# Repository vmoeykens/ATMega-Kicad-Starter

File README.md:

# ATMega328P KiCad Starter Board
Vincent Moeykens

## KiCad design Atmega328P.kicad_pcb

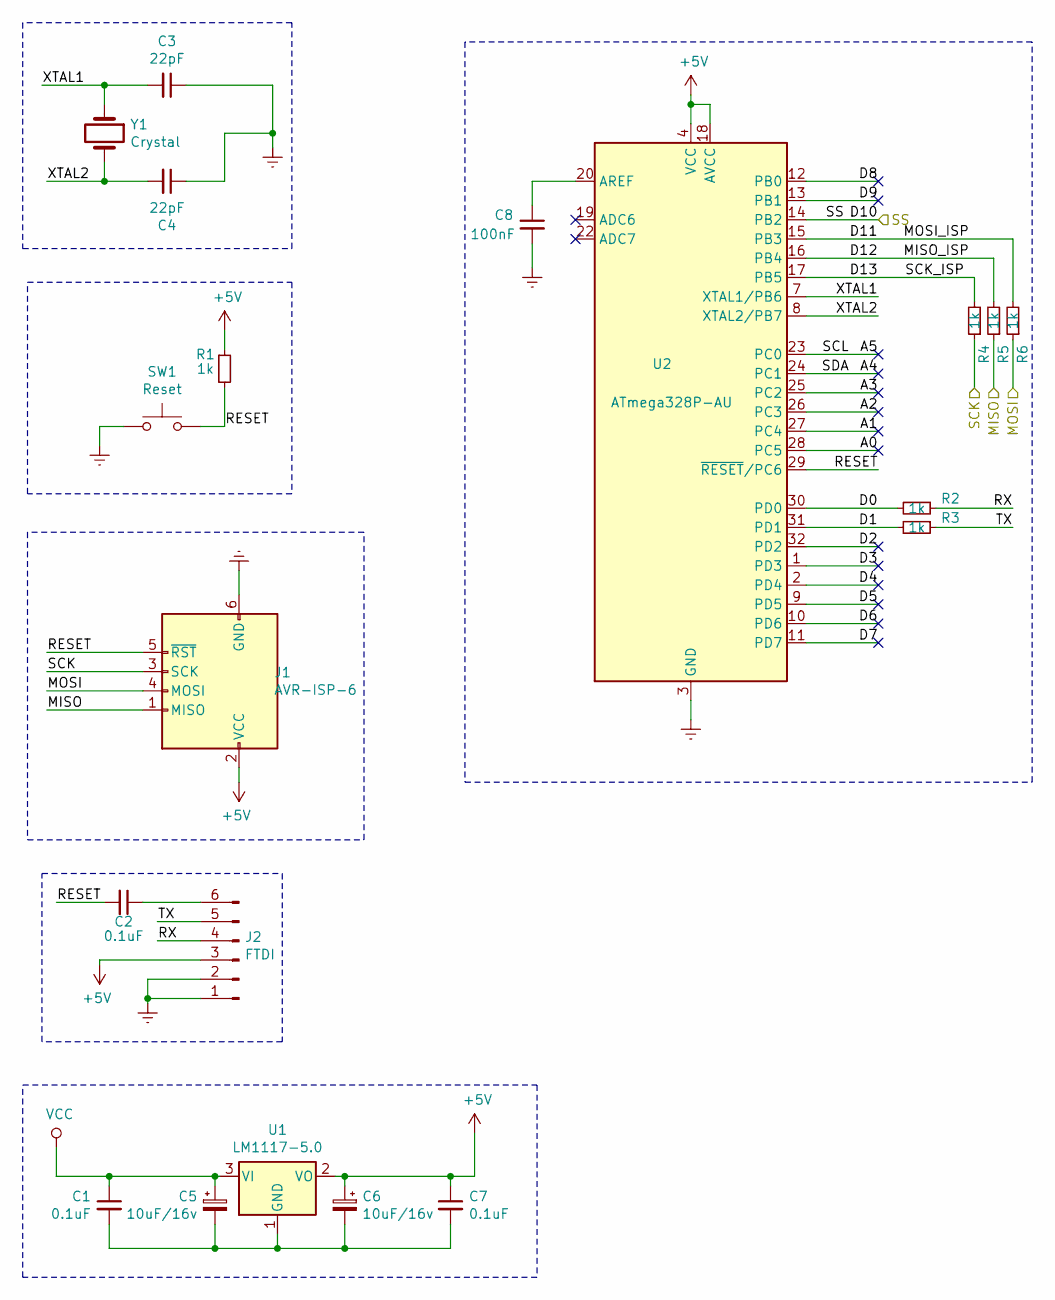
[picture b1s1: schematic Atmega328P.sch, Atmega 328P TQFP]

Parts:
C1, C2, C7: 0.1uF; C_0805_2012Metric_Pad1.15x1.40mm_HandSolder
C3, C4: 22pF; C_0805_2012Metric_Pad1.15x1.40mm_HandSolder
C5, C6: 10uF/16v; C_0805_2012Metric_Pad1.15x1.40mm_HandSolder
C8: 100nF; C_0805_2012Metric_Pad1.15x1.40mm_HandSolder
J1: AVR-ISP-6; IDC-Header_2x03_Pitch2.54mm_Straight
J2: FTDI; TerminalBlock_bornier-6_P5.08mm
R1, R2, R3, R4, R5, R6: 1k; R_0805_2012Metric_Pad1.15x1.40mm_HandSolder
SW1: Reset; SW_Push_SPST_NO_Alps_SKRK
U1: LM1117-5.0; SOT230P696X180-4N
U2: ATmega328P-AU; TQFP-32_7x7mm_P0.8mm
Y1: Crystal; Crystal_HC49-4H_Vertical

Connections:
+5V: C6.1, C7.1, J1.2 (VCC), J2.3, R1.1, U1.2 (VO), U2.4 (VCC), U2.6 (VCC), U2.18 (AVCC)
/A0: U2.28 (PC5)
/A1: U2.27 (PC4)
/A2: U2.26 (PC3)
/A3: U2.25 (PC2)
/A4: U2.24 (PC1)
/A5: U2.23 (PC0)
/D0: R2.2, U2.30 (PD0)
/D1: R3.2, U2.31 (PD1)
/D2: U2.32 (PD2)
/D3: U2.1 (PD3)
/D4: U2.2 (PD4)
/D5: U2.9 (PD5)
/D6: U2.10 (PD6)
/D7: U2.11 (PD7)
/D8: U2.12 (PB0)
/D9: U2.13 (PB1)
/D11: R6.2, U2.15 (PB3)
/D12: R5.2, U2.16 (PB4)
/D13: R4.2, U2.17 (PB5)
/MISO: J1.1 (MISO), R5.1
/MOSI: J1.4 (MOSI), R6.1
/RESET: C2.2, J1.5 (~RST), R1.2, SW1.2, U2.29 (~RESET~/PC6)
/RX: J2.4, R2.1
/SCK: J1.3 (SCK), R4.1
/SS: U2.14 (PB2)
/TX: J2.5, R3.1
/XTAL1: C3.2, U2.7 (XTAL1/PB6), Y1.1
/XTAL2: C4.2, U2.8 (XTAL2/PB7), Y1.2
Earth: C3.1, C4.1, C8.2, J1.6 (GND), J2.1, J2.2, SW1.1, U2.3 (GND), U2.5 (GND), U2.21 (GND)
unnamed: C1.2, C5.2, C6.2, C7.2, U1.1 (GND)
unnamed: C2.1, J2.6
unnamed: C8.1, U2.20 (AREF)
VCC: C1.1, C5.1, U1.3 (VI)

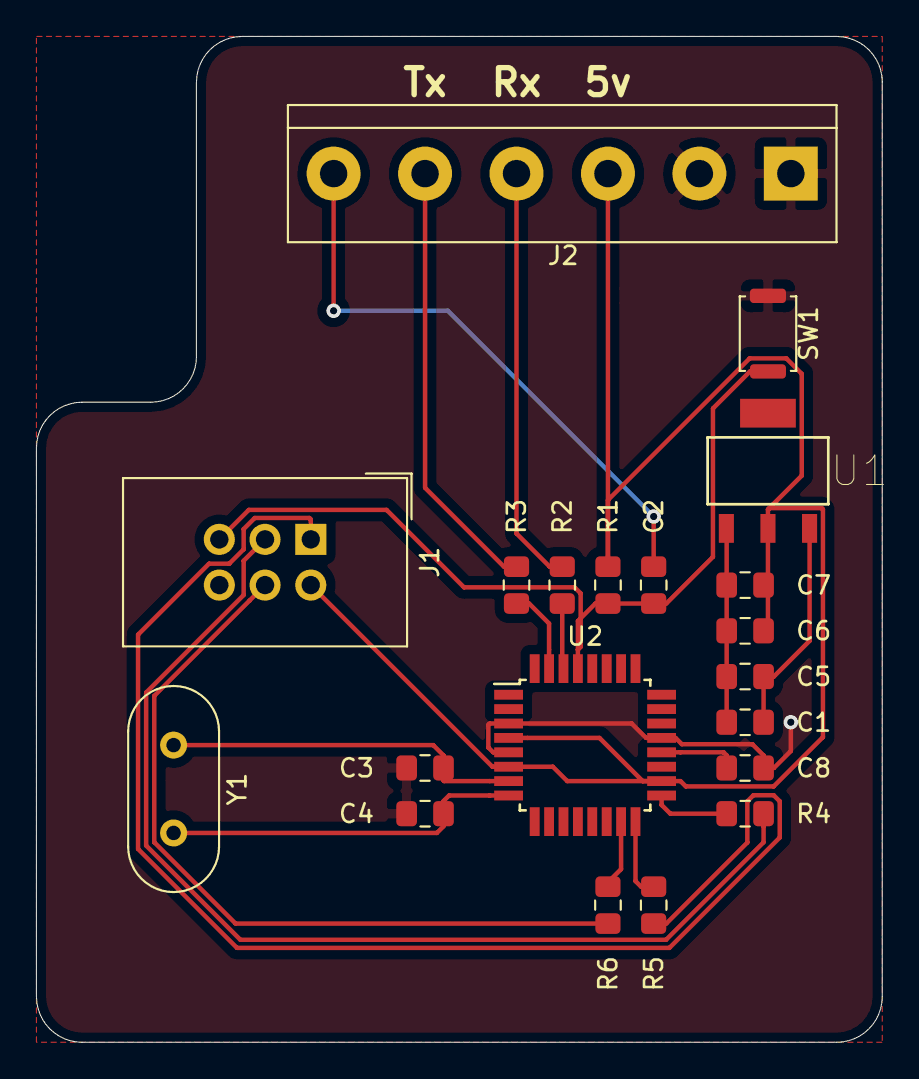
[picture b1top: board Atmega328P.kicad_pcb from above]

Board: 2 copper layers, 47.0 x 55.9 mm, 20 parts (0 on the bottom side), 19 nets.

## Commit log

2020-03-28 Adds an alternative board layout and new footprints.
2020-03-28 Adds README
2020-03-28 Modifies board layout
